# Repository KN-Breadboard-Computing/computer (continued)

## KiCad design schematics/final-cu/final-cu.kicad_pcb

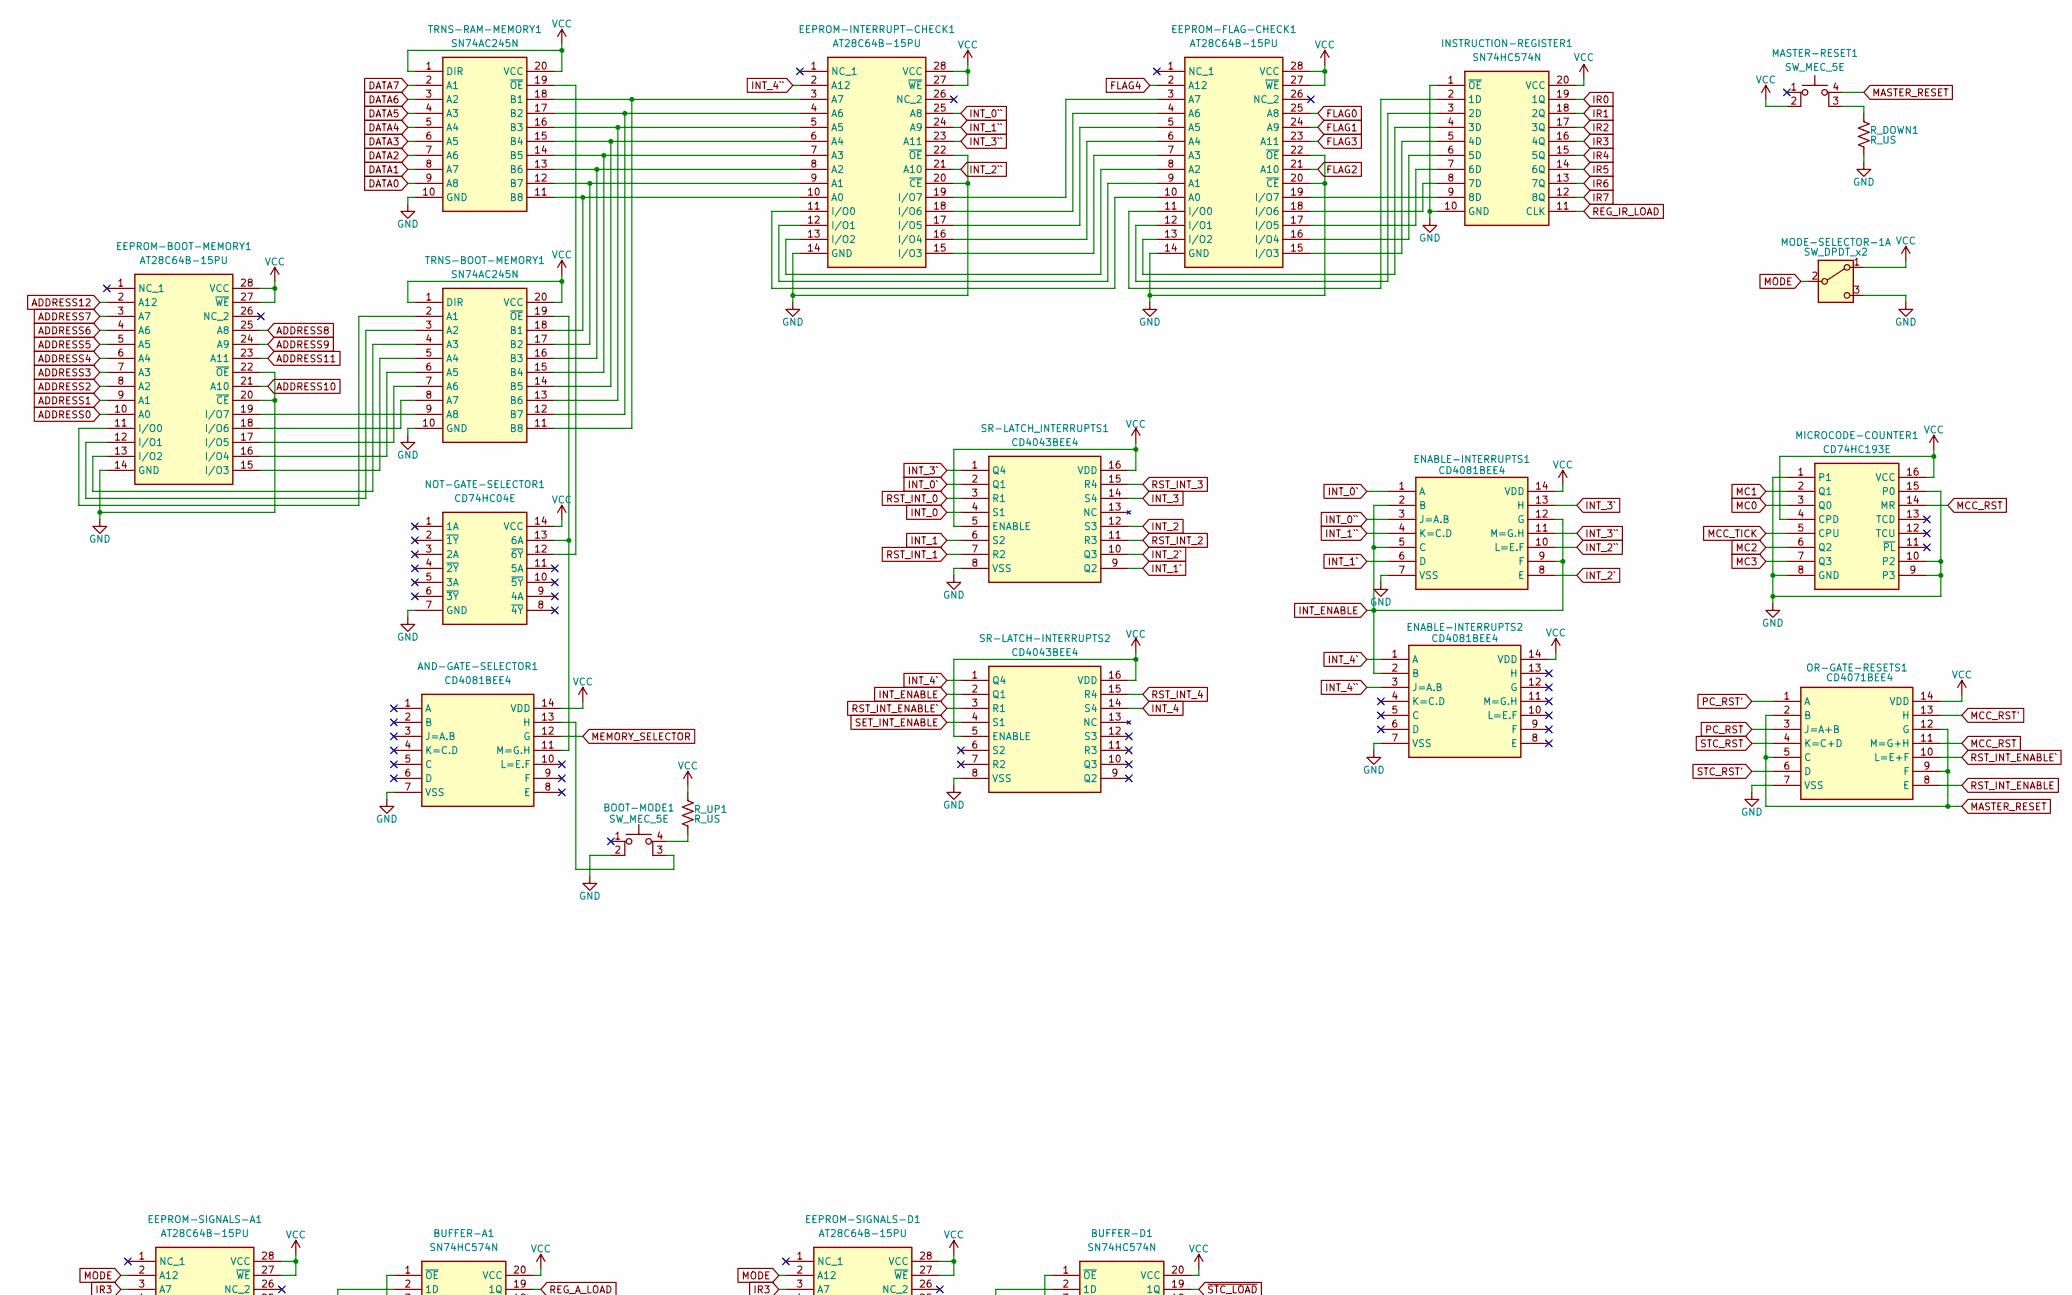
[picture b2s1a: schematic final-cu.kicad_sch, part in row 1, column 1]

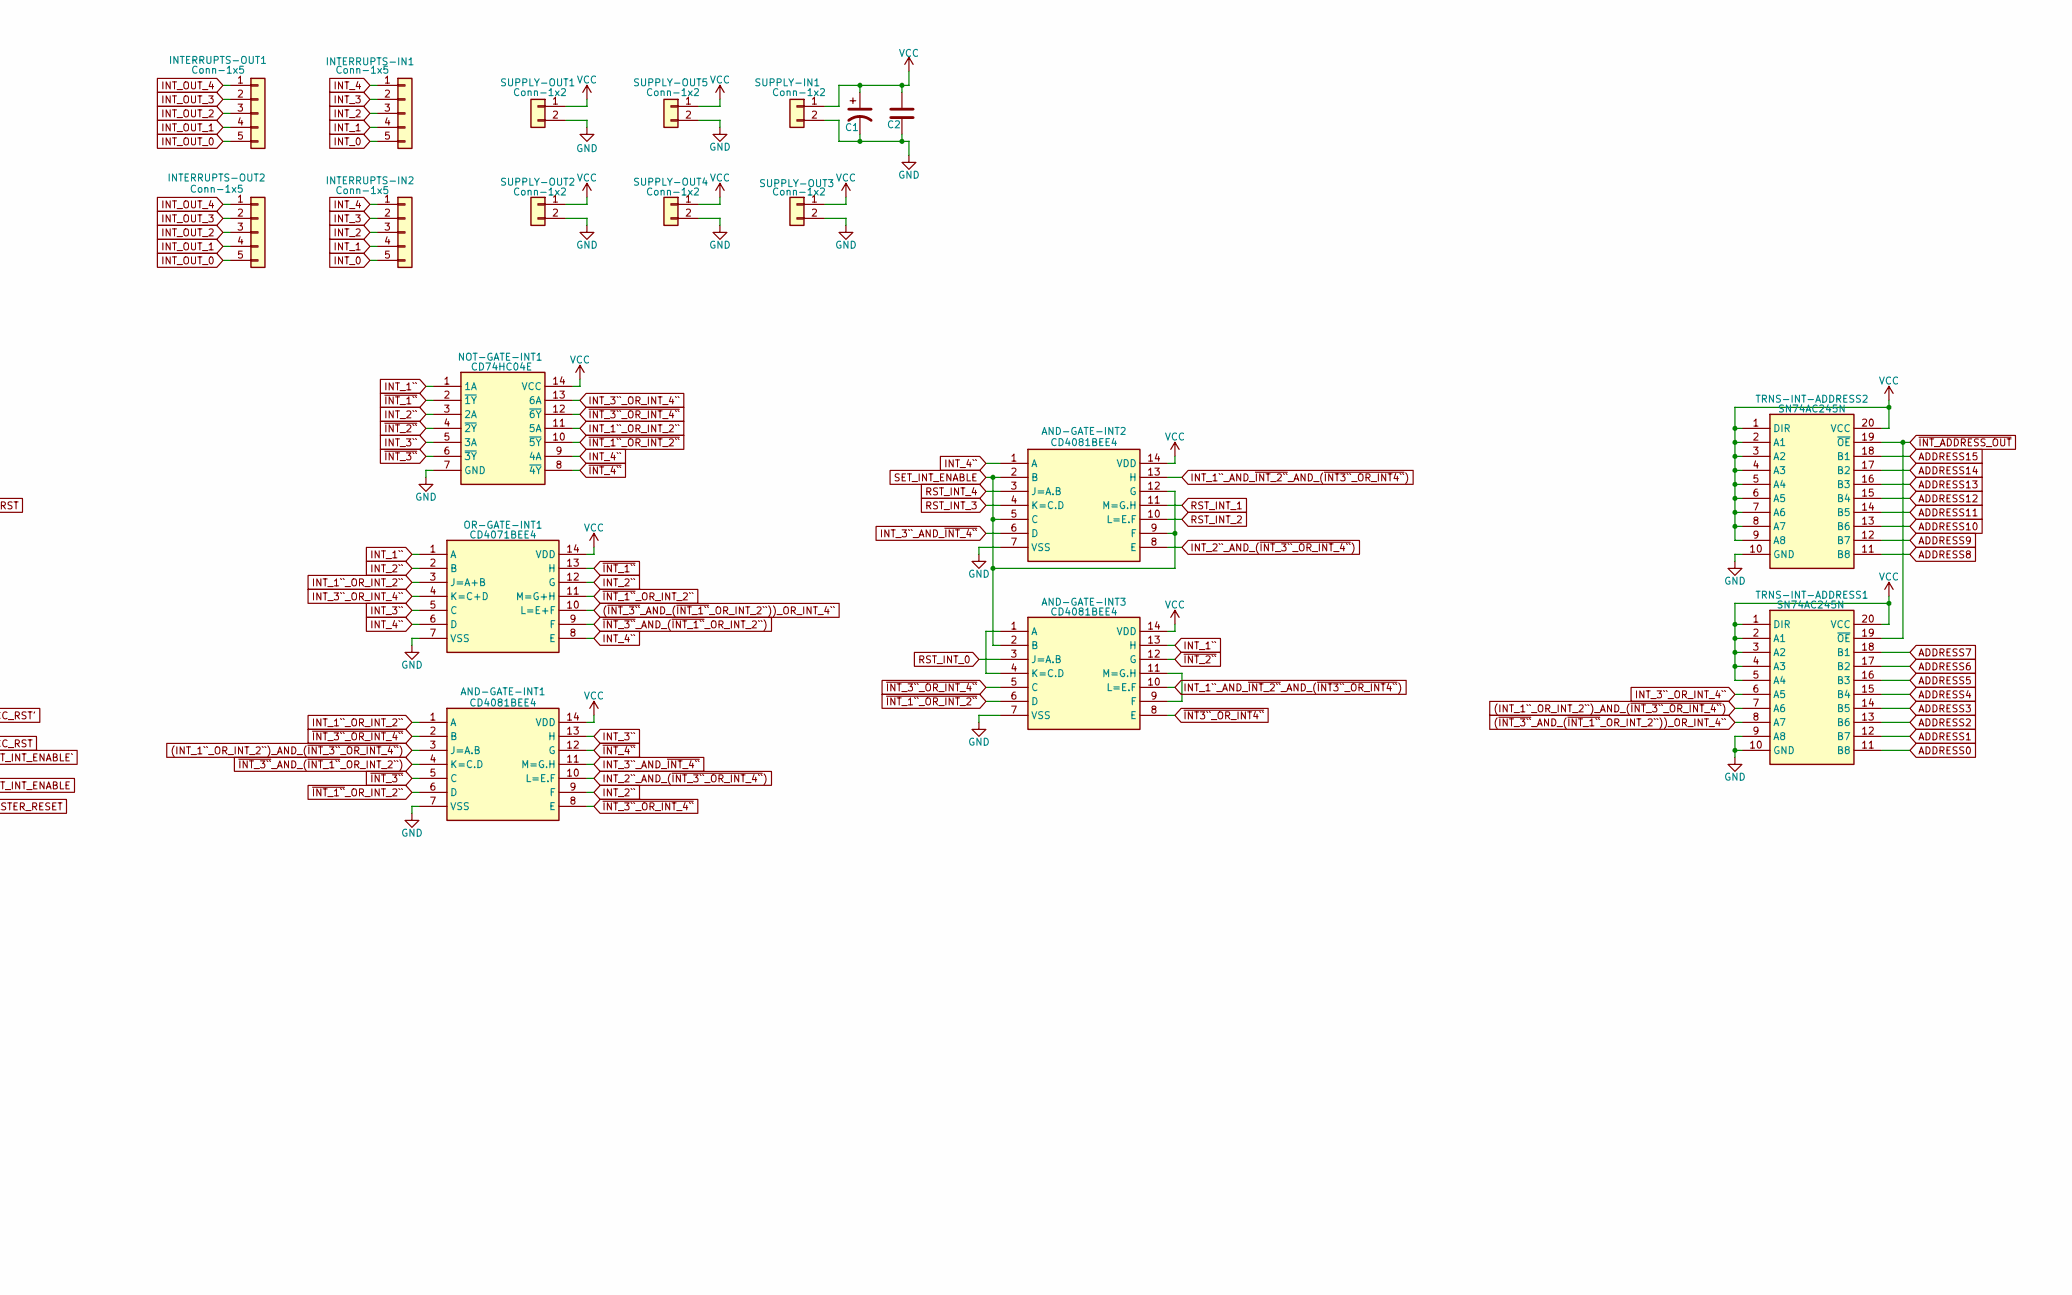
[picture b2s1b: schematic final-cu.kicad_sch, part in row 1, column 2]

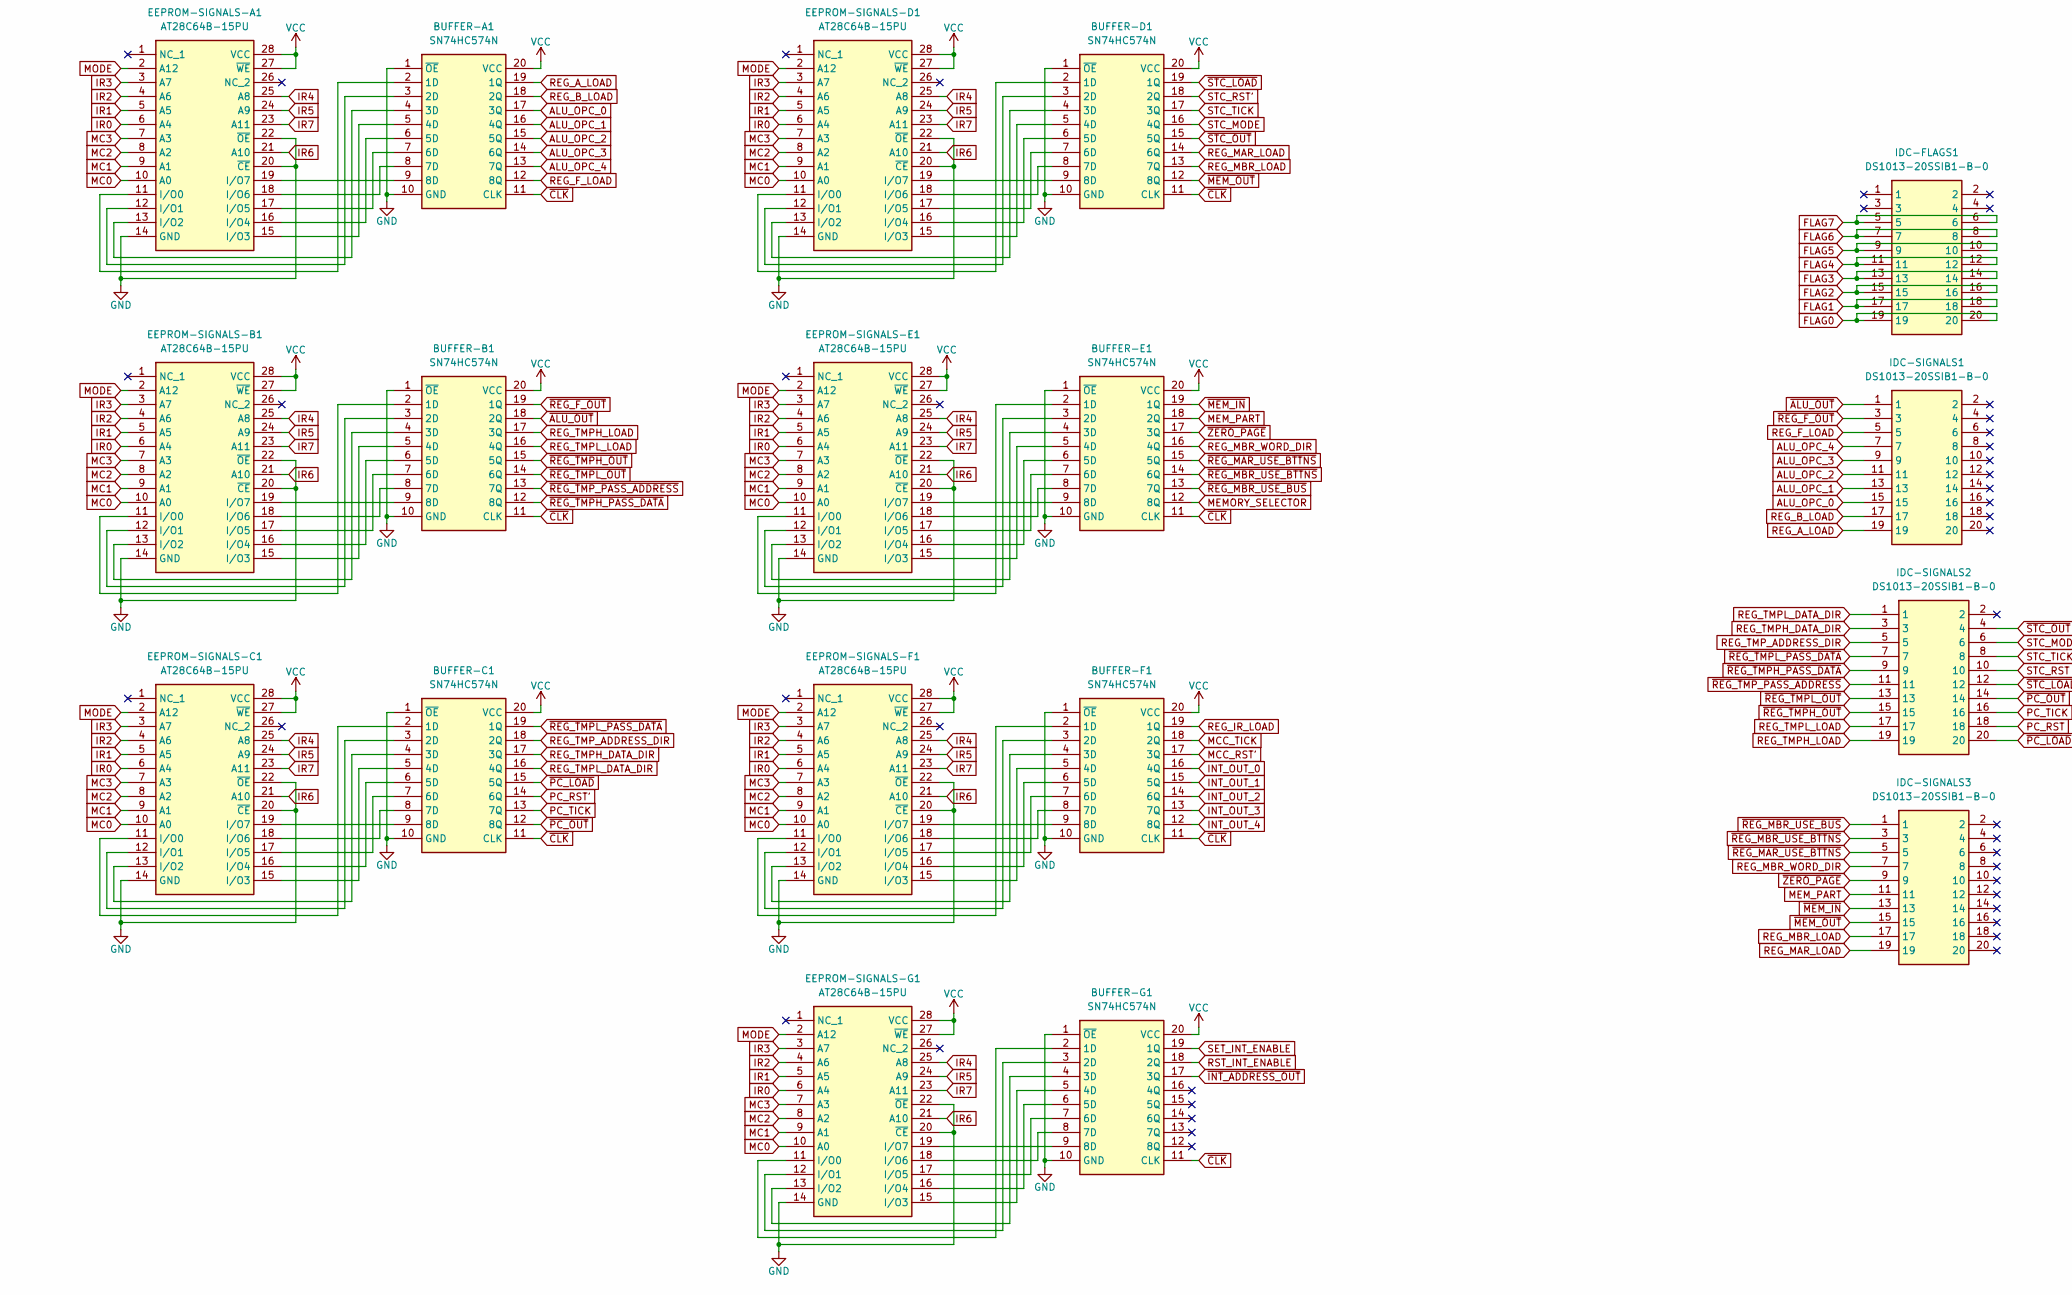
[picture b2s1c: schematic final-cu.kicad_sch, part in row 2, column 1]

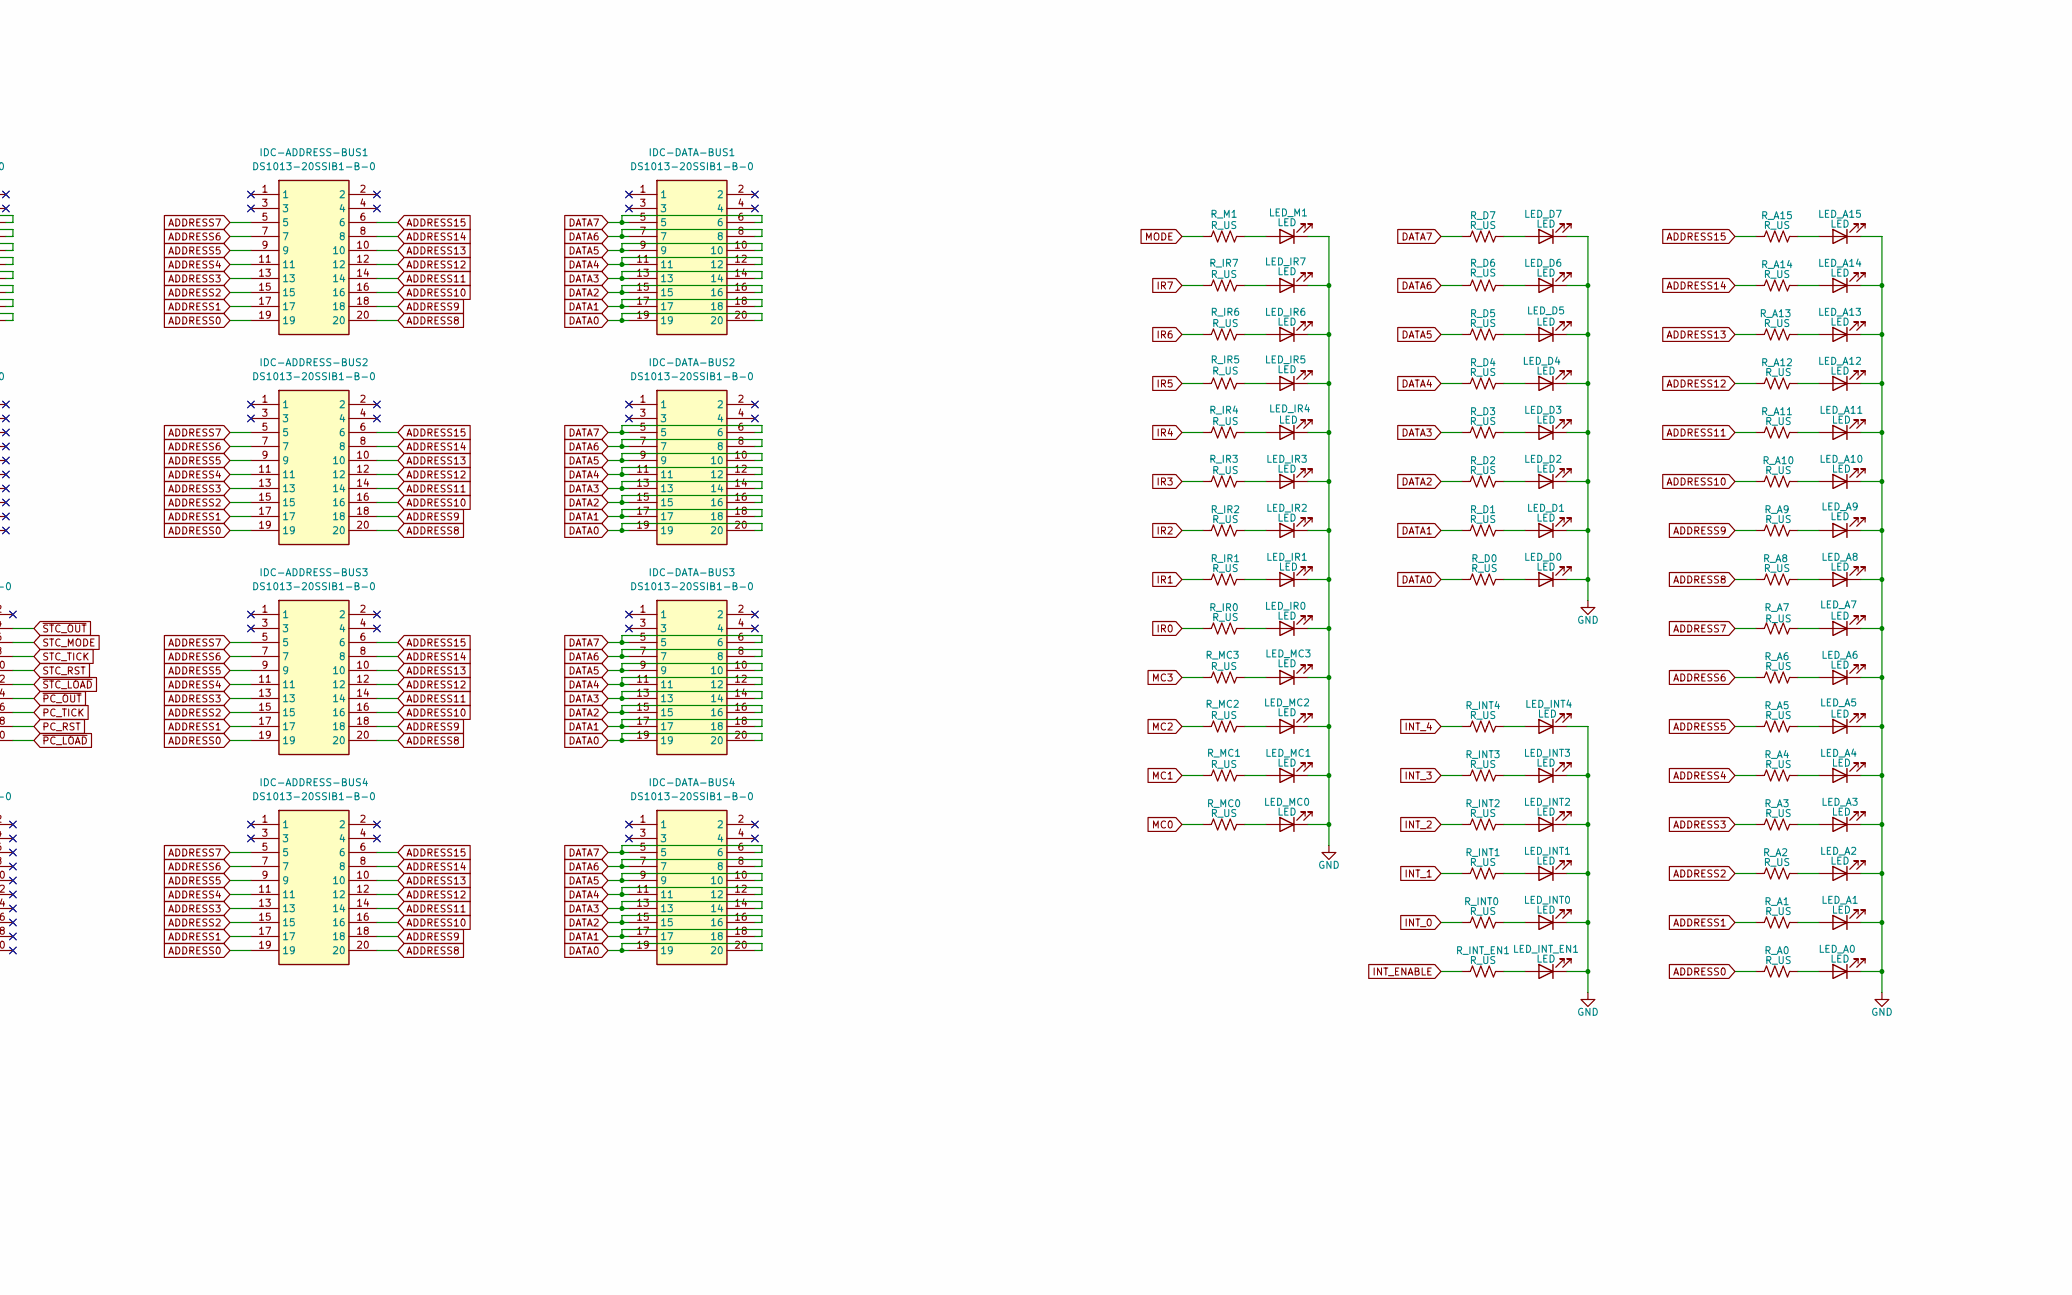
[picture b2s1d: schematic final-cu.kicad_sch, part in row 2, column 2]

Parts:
AND-GATE-INT1, AND-GATE-INT2, AND-GATE-INT3: CD4081BEE4; DIP-14_W7.62mm; Mouser Part Number 595-CD4081BEE4
AND-GATE-SELECTOR1: CD4081BEE4; DIP-14_W7.62mm; Mouser Part Number 595-CD4081BEE4
BOOT-MODE1: SW_MEC_5E; SW_Push_2P1T_Toggle_CK_PVA1xxH1xxxxxxV2
BUFFER-A1: SN74HC574N; DIP-20_W7.62mm; Mouser Part Number 595-SN74HC574N
BUFFER-B1: SN74HC574N; DIP-20_W7.62mm; Mouser Part Number 595-SN74HC574N
BUFFER-C1: SN74HC574N; DIP-20_W7.62mm; Mouser Part Number 595-SN74HC574N
BUFFER-D1: SN74HC574N; DIP-20_W7.62mm; Mouser Part Number 595-SN74HC574N
BUFFER-E1: SN74HC574N; DIP-20_W7.62mm; Mouser Part Number 595-SN74HC574N
BUFFER-F1: SN74HC574N; DIP-20_W7.62mm; Mouser Part Number 595-SN74HC574N
BUFFER-G1: SN74HC574N; DIP-20_W7.62mm; Mouser Part Number 595-SN74HC574N
C1: C_Polarized_US; CP_Radial_D5.0mm_P2.50mm
C2: C; C_Disc_D3.0mm_W1.6mm_P2.50mm
EEPROM-BOOT-MEMORY1: AT28C64B-15PU; DIP-28_W15.24mm; Mouser Part Number 556-AT28C64B15PU
EEPROM-FLAG-CHECK1: AT28C64B-15PU; DIP-28_W15.24mm; Mouser Part Number 556-AT28C64B15PU
EEPROM-INTERRUPT-CHECK1: AT28C64B-15PU; DIP-28_W15.24mm; Mouser Part Number 556-AT28C64B15PU
EEPROM-SIGNALS-A1: AT28C64B-15PU; DIP-28_W15.24mm; Mouser Part Number 556-AT28C64B15PU
EEPROM-SIGNALS-B1: AT28C64B-15PU; DIP-28_W15.24mm; Mouser Part Number 556-AT28C64B15PU
EEPROM-SIGNALS-C1: AT28C64B-15PU; DIP-28_W15.24mm; Mouser Part Number 556-AT28C64B15PU
EEPROM-SIGNALS-D1: AT28C64B-15PU; DIP-28_W15.24mm; Mouser Part Number 556-AT28C64B15PU
EEPROM-SIGNALS-E1: AT28C64B-15PU; DIP-28_W15.24mm; Mouser Part Number 556-AT28C64B15PU
EEPROM-SIGNALS-F1: AT28C64B-15PU; DIP-28_W15.24mm; Mouser Part Number 556-AT28C64B15PU
EEPROM-SIGNALS-G1: AT28C64B-15PU; DIP-28_W15.24mm; Mouser Part Number 556-AT28C64B15PU
ENABLE-INTERRUPTS1, ENABLE-INTERRUPTS2: CD4081BEE4; DIP-14_W7.62mm; Mouser Part Number 595-CD4081BEE4
IDC-ADDRESS-BUS1, IDC-ADDRESS-BUS2, IDC-ADDRESS-BUS3, IDC-ADDRESS-BUS4: DS1013-20SSIB1-B-0; PinSocket_2x10_P2.54mm_Vertical; Manufacturer_Part_Number DS1013-20SSIB1-B-0
IDC-DATA-BUS1, IDC-DATA-BUS2, IDC-DATA-BUS3, IDC-DATA-BUS4: DS1013-20SSIB1-B-0; PinSocket_2x10_P2.54mm_Vertical; Manufacturer_Part_Number DS1013-20SSIB1-B-0
IDC-FLAGS1: DS1013-20SSIB1-B-0; PinSocket_2x10_P2.54mm_Vertical; Manufacturer_Part_Number DS1013-20SSIB1-B-0
IDC-SIGNALS1, IDC-SIGNALS2, IDC-SIGNALS3: DS1013-20SSIB1-B-0; PinSocket_2x10_P2.54mm_Vertical; Manufacturer_Part_Number DS1013-20SSIB1-B-0
INSTRUCTION-REGISTER1: SN74HC574N; DIP-20_W7.62mm; Mouser Part Number 595-SN74HC574N
INTERRUPTS-IN1, INTERRUPTS-IN2: Conn-1x5; PinHeader_1x05_P2.54mm_Vertical
INTERRUPTS-OUT1, INTERRUPTS-OUT2: Conn-1x5; PinHeader_1x05_P2.54mm_Vertical
LED_A0, LED_A1, LED_A2, LED_A3, LED_A4, LED_A5, LED_A6, LED_A7, LED_A8, LED_A9, LED_A10, LED_A11, LED_A12, LED_A13, LED_A14, LED_A15: LED; LED_D5.0mm_FlatTop
LED_D0, LED_D1, LED_D2, LED_D3, LED_D4, LED_D5, LED_D6, LED_D7: LED; LED_D5.0mm_FlatTop
LED_INT0, LED_INT1, LED_INT2, LED_INT3, LED_INT4: LED; LED_D5.0mm_FlatTop
LED_INT_EN1: LED; LED_D5.0mm_FlatTop
LED_IR0, LED_IR1, LED_IR2, LED_IR3, LED_IR4, LED_IR5, LED_IR6, LED_IR7: LED; LED_D5.0mm_FlatTop
LED_M1: LED; LED_D5.0mm_FlatTop
LED_MC0, LED_MC1, LED_MC2, LED_MC3: LED; LED_D5.0mm_FlatTop
MASTER-RESET1: SW_MEC_5E; SW_Push_2P1T_Toggle_CK_PVA1xxH1xxxxxxV2
MICROCODE-COUNTER1: CD74HC193E; DIP-16_W7.62mm; Mouser Part Number 595-CD74HC193E
MODE-SELECTOR-1: SW_DPDT_x2; SW_Slide-03_Wuerth-WS-SLTV_10x2.5x6.4_P2.54mm
NOT-GATE-INT1: CD74HC04E; DIP-14_W7.62mm; Mouser Part Number 595-CD74HC04E
NOT-GATE-SELECTOR1: CD74HC04E; DIP-14_W7.62mm; Mouser Part Number 595-CD74HC04E
OR-GATE-INT1: CD4071BEE4; DIP-14_W7.62mm; Mouser Part Number 595-CD4071BEE4
OR-GATE-RESETS1: CD4071BEE4; DIP-14_W7.62mm; Mouser Part Number 595-CD4071BEE4
R_A0, R_A1, R_A2, R_A3, R_A4, R_A5, R_A6, R_A7, R_A8, R_A9, R_A10, R_A11, R_A12, R_A13, R_A14, R_A15: R_US; R_Axial_DIN0204_L3.6mm_D1.6mm_P7.62mm_Horizontal
R_D0, R_D1, R_D2, R_D3, R_D4, R_D5, R_D6, R_D7: R_US; R_Axial_DIN0204_L3.6mm_D1.6mm_P7.62mm_Horizontal
R_DOWN1: R_US; R_Axial_DIN0204_L3.6mm_D1.6mm_P7.62mm_Horizontal
R_INT0, R_INT1, R_INT2, R_INT3, R_INT4: R_US; R_Axial_DIN0204_L3.6mm_D1.6mm_P7.62mm_Horizontal
R_INT_EN1: R_US; R_Axial_DIN0204_L3.6mm_D1.6mm_P7.62mm_Horizontal
R_IR0, R_IR1, R_IR2, R_IR3, R_IR4, R_IR5, R_IR6, R_IR7: R_US; R_Axial_DIN0204_L3.6mm_D1.6mm_P7.62mm_Horizontal
R_M1: R_US; R_Axial_DIN0204_L3.6mm_D1.6mm_P7.62mm_Horizontal
R_MC0, R_MC1, R_MC2, R_MC3: R_US; R_Axial_DIN0204_L3.6mm_D1.6mm_P7.62mm_Horizontal
R_UP1: R_US; R_Axial_DIN0204_L3.6mm_D1.6mm_P7.62mm_Horizontal
SR-LATCH-INTERRUPTS2: CD4043BEE4; DIP-16_W7.62mm; Mouser Part Number 595-CD4043BEE4
SR-LATCH_INTERRUPTS1: CD4043BEE4; DIP-16_W7.62mm; Mouser Part Number 595-CD4043BEE4
SUPPLY-IN1: Conn-1x2; PinHeader_1x02_P2.54mm_Vertical
SUPPLY-OUT1, SUPPLY-OUT2, SUPPLY-OUT3, SUPPLY-OUT4, SUPPLY-OUT5: Conn-1x2; PinHeader_1x02_P2.54mm_Vertical
TRNS-BOOT-MEMORY1: SN74AC245N; DIP-20_W7.62mm; Mouser Part Number 595-SN74AC245N
TRNS-INT-ADDRESS1, TRNS-INT-ADDRESS2: SN74AC245N; DIP-20_W7.62mm; Mouser Part Number 595-SN74AC245N
TRNS-RAM-MEMORY1: SN74AC245N; DIP-20_W7.62mm; Mouser Part Number 595-SN74AC245N

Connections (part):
(INT_1``_OR_INT_2``)_AND_(~INT_3``_OR_INT_4``): AND-GATE-INT1.3 (J=A.B), TRNS-INT-ADDRESS1.7 (A6)
(~INT_3``_AND_(~INT_1``_OR_INT_2``))_OR_INT_4``: OR-GATE-INT1.10 (L=E+F), TRNS-INT-ADDRESS1.8 (A7)
ADDRESS0: EEPROM-BOOT-MEMORY1.10 (A0), IDC-ADDRESS-BUS1.19, IDC-ADDRESS-BUS2.19, IDC-ADDRESS-BUS3.19, IDC-ADDRESS-BUS4.19, R_A0.1, TRNS-INT-ADDRESS1.11 (B8)
ADDRESS1: EEPROM-BOOT-MEMORY1.9 (A1), IDC-ADDRESS-BUS1.17, IDC-ADDRESS-BUS2.17, IDC-ADDRESS-BUS3.17, IDC-ADDRESS-BUS4.17, R_A1.1, TRNS-INT-ADDRESS1.12 (B7)
ADDRESS2: EEPROM-BOOT-MEMORY1.8 (A2), IDC-ADDRESS-BUS1.15, IDC-ADDRESS-BUS2.15, IDC-ADDRESS-BUS3.15, IDC-ADDRESS-BUS4.15, R_A2.1, TRNS-INT-ADDRESS1.13 (B6)
ADDRESS3: EEPROM-BOOT-MEMORY1.7 (A3), IDC-ADDRESS-BUS1.13, IDC-ADDRESS-BUS2.13, IDC-ADDRESS-BUS3.13, IDC-ADDRESS-BUS4.13, R_A3.1, TRNS-INT-ADDRESS1.14 (B5)
ADDRESS4: EEPROM-BOOT-MEMORY1.6 (A4), IDC-ADDRESS-BUS1.11, IDC-ADDRESS-BUS2.11, IDC-ADDRESS-BUS3.11, IDC-ADDRESS-BUS4.11, R_A4.1, TRNS-INT-ADDRESS1.15 (B4)
ADDRESS5: EEPROM-BOOT-MEMORY1.5 (A5), IDC-ADDRESS-BUS1.9, IDC-ADDRESS-BUS2.9, IDC-ADDRESS-BUS3.9, IDC-ADDRESS-BUS4.9, R_A5.1, TRNS-INT-ADDRESS1.16 (B3)
ADDRESS6: EEPROM-BOOT-MEMORY1.4 (A6), IDC-ADDRESS-BUS1.7, IDC-ADDRESS-BUS2.7, IDC-ADDRESS-BUS3.7, IDC-ADDRESS-BUS4.7, R_A6.1, TRNS-INT-ADDRESS1.17 (B2)
ADDRESS7: EEPROM-BOOT-MEMORY1.3 (A7), IDC-ADDRESS-BUS1.5, IDC-ADDRESS-BUS2.5, IDC-ADDRESS-BUS3.5, IDC-ADDRESS-BUS4.5, R_A7.1, TRNS-INT-ADDRESS1.18 (B1)
ADDRESS8: EEPROM-BOOT-MEMORY1.25 (A8), IDC-ADDRESS-BUS1.20, IDC-ADDRESS-BUS2.20, IDC-ADDRESS-BUS3.20, IDC-ADDRESS-BUS4.20, R_A8.1, TRNS-INT-ADDRESS2.11 (B8)
ADDRESS9: EEPROM-BOOT-MEMORY1.24 (A9), IDC-ADDRESS-BUS1.18, IDC-ADDRESS-BUS2.18, IDC-ADDRESS-BUS3.18, IDC-ADDRESS-BUS4.18, R_A9.1, TRNS-INT-ADDRESS2.12 (B7)
ADDRESS10: EEPROM-BOOT-MEMORY1.21 (A10), IDC-ADDRESS-BUS1.16, IDC-ADDRESS-BUS2.16, IDC-ADDRESS-BUS3.16, IDC-ADDRESS-BUS4.16, R_A10.1, TRNS-INT-ADDRESS2.13 (B6)
ADDRESS11: EEPROM-BOOT-MEMORY1.23 (A11), IDC-ADDRESS-BUS1.14, IDC-ADDRESS-BUS2.14, IDC-ADDRESS-BUS3.14, IDC-ADDRESS-BUS4.14, R_A11.1, TRNS-INT-ADDRESS2.14 (B5)
ADDRESS12: EEPROM-BOOT-MEMORY1.2 (A12), IDC-ADDRESS-BUS1.12, IDC-ADDRESS-BUS2.12, IDC-ADDRESS-BUS3.12, IDC-ADDRESS-BUS4.12, R_A12.1, TRNS-INT-ADDRESS2.15 (B4)
ADDRESS13: IDC-ADDRESS-BUS1.10, IDC-ADDRESS-BUS2.10, IDC-ADDRESS-BUS3.10, IDC-ADDRESS-BUS4.10, R_A13.1, TRNS-INT-ADDRESS2.16 (B3)
ADDRESS14: IDC-ADDRESS-BUS1.8, IDC-ADDRESS-BUS2.8, IDC-ADDRESS-BUS3.8, IDC-ADDRESS-BUS4.8, R_A14.1, TRNS-INT-ADDRESS2.17 (B2)
ADDRESS15: IDC-ADDRESS-BUS1.6, IDC-ADDRESS-BUS2.6, IDC-ADDRESS-BUS3.6, IDC-ADDRESS-BUS4.6, R_A15.2, TRNS-INT-ADDRESS2.18 (B1)
ALU_OPC_0: BUFFER-A1.17 (3Q), IDC-SIGNALS1.15
ALU_OPC_1: BUFFER-A1.16 (4Q), IDC-SIGNALS1.13
ALU_OPC_2: BUFFER-A1.15 (5Q), IDC-SIGNALS1.11
ALU_OPC_3: BUFFER-A1.14 (6Q), IDC-SIGNALS1.9
ALU_OPC_4: BUFFER-A1.13 (7Q), IDC-SIGNALS1.7
DATA0: IDC-DATA-BUS1.19, IDC-DATA-BUS1.20, IDC-DATA-BUS2.19, IDC-DATA-BUS2.20, IDC-DATA-BUS3.19, IDC-DATA-BUS3.20, IDC-DATA-BUS4.19, IDC-DATA-BUS4.20, R_D0.1, TRNS-RAM-MEMORY1.9 (A8)
DATA1: IDC-DATA-BUS1.17, IDC-DATA-BUS1.18, IDC-DATA-BUS2.17, IDC-DATA-BUS2.18, IDC-DATA-BUS3.17, IDC-DATA-BUS3.18, IDC-DATA-BUS4.17, IDC-DATA-BUS4.18, R_D1.1, TRNS-RAM-MEMORY1.8 (A7)
DATA2: IDC-DATA-BUS1.15, IDC-DATA-BUS1.16, IDC-DATA-BUS2.15, IDC-DATA-BUS2.16, IDC-DATA-BUS3.15, IDC-DATA-BUS3.16, IDC-DATA-BUS4.15, IDC-DATA-BUS4.16, R_D2.1, TRNS-RAM-MEMORY1.7 (A6)
DATA3: IDC-DATA-BUS1.13, IDC-DATA-BUS1.14, IDC-DATA-BUS2.13, IDC-DATA-BUS2.14, IDC-DATA-BUS3.13, IDC-DATA-BUS3.14, IDC-DATA-BUS4.13, IDC-DATA-BUS4.14, R_D3.1, TRNS-RAM-MEMORY1.6 (A5)
DATA4: IDC-DATA-BUS1.11, IDC-DATA-BUS1.12, IDC-DATA-BUS2.11, IDC-DATA-BUS2.12, IDC-DATA-BUS3.11, IDC-DATA-BUS3.12, IDC-DATA-BUS4.11, IDC-DATA-BUS4.12, R_D4.1, TRNS-RAM-MEMORY1.5 (A4)
DATA5: IDC-DATA-BUS1.9, IDC-DATA-BUS1.10, IDC-DATA-BUS2.9, IDC-DATA-BUS2.10, IDC-DATA-BUS3.9, IDC-DATA-BUS3.10, IDC-DATA-BUS4.9, IDC-DATA-BUS4.10, R_D5.1, TRNS-RAM-MEMORY1.4 (A3)
DATA6: IDC-DATA-BUS1.7, IDC-DATA-BUS1.8, IDC-DATA-BUS2.7, IDC-DATA-BUS2.8, IDC-DATA-BUS3.7, IDC-DATA-BUS3.8, IDC-DATA-BUS4.7, IDC-DATA-BUS4.8, R_D6.1, TRNS-RAM-MEMORY1.3 (A2)
DATA7: IDC-DATA-BUS1.5, IDC-DATA-BUS1.6, IDC-DATA-BUS2.5, IDC-DATA-BUS2.6, IDC-DATA-BUS3.5, IDC-DATA-BUS3.6, IDC-DATA-BUS4.5, IDC-DATA-BUS4.6, R_D7.1, TRNS-RAM-MEMORY1.2 (A1)
FLAG0: EEPROM-FLAG-CHECK1.25 (A8), IDC-FLAGS1.19, IDC-FLAGS1.20
FLAG1: EEPROM-FLAG-CHECK1.24 (A9), IDC-FLAGS1.17, IDC-FLAGS1.18
FLAG2: EEPROM-FLAG-CHECK1.21 (A10), IDC-FLAGS1.15, IDC-FLAGS1.16
FLAG3: EEPROM-FLAG-CHECK1.23 (A11), IDC-FLAGS1.13, IDC-FLAGS1.14
FLAG4: EEPROM-FLAG-CHECK1.2 (A12), IDC-FLAGS1.11, IDC-FLAGS1.12
FLAG5: IDC-FLAGS1.9, IDC-FLAGS1.10
FLAG6: IDC-FLAGS1.7, IDC-FLAGS1.8
FLAG7: IDC-FLAGS1.5, IDC-FLAGS1.6
GND: AND-GATE-INT1.7 (VSS), AND-GATE-INT2.7 (VSS), AND-GATE-INT3.7 (VSS), AND-GATE-SELECTOR1.7 (VSS), BOOT-MODE1.2, BUFFER-A1.1 (~OE), BUFFER-A1.10 (GND), BUFFER-B1.1 (~OE), BUFFER-B1.10 (GND), BUFFER-C1.1 (~OE), BUFFER-C1.10 (GND), BUFFER-D1.1 (~OE), BUFFER-D1.10 (GND), BUFFER-E1.1 (~OE), BUFFER-E1.10 (GND), BUFFER-F1.1 (~OE), BUFFER-F1.10 (GND), BUFFER-G1.1 (~OE), BUFFER-G1.10 (GND), C1.2, C2.2, EEPROM-BOOT-MEMORY1.14 (GND), EEPROM-BOOT-MEMORY1.20 (~CE), EEPROM-BOOT-MEMORY1.22 (~OE), EEPROM-FLAG-CHECK1.14 (GND), EEPROM-FLAG-CHECK1.20 (~CE), EEPROM-FLAG-CHECK1.22 (~OE), EEPROM-INTERRUPT-CHECK1.14 (GND), EEPROM-INTERRUPT-CHECK1.20 (~CE), EEPROM-INTERRUPT-CHECK1.22 (~OE), EEPROM-SIGNALS-A1.14 (GND), EEPROM-SIGNALS-A1.20 (~CE), EEPROM-SIGNALS-A1.22 (~OE), EEPROM-SIGNALS-B1.14 (GND), EEPROM-SIGNALS-B1.20 (~CE), EEPROM-SIGNALS-B1.22 (~OE), EEPROM-SIGNALS-C1.14 (GND), EEPROM-SIGNALS-C1.20 (~CE), EEPROM-SIGNALS-C1.22 (~OE), EEPROM-SIGNALS-D1.14 (GND), EEPROM-SIGNALS-D1.20 (~CE), EEPROM-SIGNALS-D1.22 (~OE), EEPROM-SIGNALS-E1.14 (GND), EEPROM-SIGNALS-E1.20 (~CE), EEPROM-SIGNALS-E1.22 (~OE), EEPROM-SIGNALS-F1.14 (GND), EEPROM-SIGNALS-F1.20 (~CE), EEPROM-SIGNALS-F1.22 (~OE), EEPROM-SIGNALS-G1.14 (GND), EEPROM-SIGNALS-G1.20 (~CE), EEPROM-SIGNALS-G1.22 (~OE), ENABLE-INTERRUPTS1.7 (VSS), ENABLE-INTERRUPTS2.7 (VSS), INSTRUCTION-REGISTER1.1 (~OE), INSTRUCTION-REGISTER1.10 (GND), LED_A0.1 (K), LED_A1.1 (K), LED_A2.1 (K), LED_A3.1 (K), LED_A4.1 (K), LED_A5.1 (K), LED_A6.1 (K), LED_A7.1 (K), LED_A8.1 (K), LED_A9.1 (K), LED_A10.1 (K), LED_A11.1 (K), LED_A12.1 (K), LED_A13.1 (K), LED_A14.1 (K), LED_A15.1 (K), LED_D0.1 (K), LED_D1.1 (K), LED_D2.1 (K), LED_D3.1 (K), LED_D4.1 (K), LED_D5.1 (K), LED_D6.1 (K), LED_D7.1 (K), LED_INT0.1 (K)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
INT_0: INTERRUPTS-IN1.5, INTERRUPTS-IN2.5, R_INT0.1, SR-LATCH_INTERRUPTS1.4 (S1)
INT_0`: ENABLE-INTERRUPTS1.1 (A), SR-LATCH_INTERRUPTS1.2 (Q1)
INT_0``: EEPROM-INTERRUPT-CHECK1.25 (A8), ENABLE-INTERRUPTS1.3 (J=A.B)
INT_1: INTERRUPTS-IN1.4, INTERRUPTS-IN2.4, R_INT1.1, SR-LATCH_INTERRUPTS1.6 (S2)
INT_1`: ENABLE-INTERRUPTS1.6 (D), SR-LATCH_INTERRUPTS1.9 (Q2)
INT_1``: AND-GATE-INT3.13 (H), EEPROM-INTERRUPT-CHECK1.24 (A9), ENABLE-INTERRUPTS1.4 (K=C.D), NOT-GATE-INT1.1 (1A), OR-GATE-INT1.1 (A)
INT_1``_AND_~INT_2``_AND_(~INT3``_OR_INT4``): AND-GATE-INT2.13 (H), AND-GATE-INT3.10 (L=E.F)
INT_1``_OR_INT_2``: AND-GATE-INT1.1 (A), NOT-GATE-INT1.11 (5A), OR-GATE-INT1.3 (J=A+B)
INT_2: INTERRUPTS-IN1.3, INTERRUPTS-IN2.3, R_INT2.1, SR-LATCH_INTERRUPTS1.12 (S3)
INT_2`: ENABLE-INTERRUPTS1.8 (E), SR-LATCH_INTERRUPTS1.10 (Q3)
INT_2``: AND-GATE-INT1.9 (F), EEPROM-INTERRUPT-CHECK1.21 (A10), ENABLE-INTERRUPTS1.10 (L=E.F), NOT-GATE-INT1.3 (2A), OR-GATE-INT1.2 (B), OR-GATE-INT1.12 (G)
INT_2``_AND_(~INT_3``_OR_INT_4``): AND-GATE-INT1.10 (L=E.F), AND-GATE-INT2.8 (E)
INT_3: INTERRUPTS-IN1.2, INTERRUPTS-IN2.2, R_INT3.1, SR-LATCH_INTERRUPTS1.14 (S4)
INT_3`: ENABLE-INTERRUPTS1.13 (H), SR-LATCH_INTERRUPTS1.1 (Q4)
INT_3``: AND-GATE-INT1.13 (H), EEPROM-INTERRUPT-CHECK1.23 (A11), ENABLE-INTERRUPTS1.11 (M=G.H), NOT-GATE-INT1.5 (3A), OR-GATE-INT1.5 (C)
INT_3``_AND_~INT_4``: AND-GATE-INT1.11 (M=G.H), AND-GATE-INT2.6 (D)
INT_3``_OR_INT_4``: NOT-GATE-INT1.13 (6A), OR-GATE-INT1.4 (K=C+D), TRNS-INT-ADDRESS1.6 (A5)
INT_4: INTERRUPTS-IN1.1, INTERRUPTS-IN2.1, R_INT4.1, SR-LATCH-INTERRUPTS2.14 (S4)
INT_4`: ENABLE-INTERRUPTS2.1 (A), SR-LATCH-INTERRUPTS2.1 (Q4)
INT_4``: AND-GATE-INT2.1 (A), EEPROM-INTERRUPT-CHECK1.2 (A12), ENABLE-INTERRUPTS2.3 (J=A.B), NOT-GATE-INT1.9 (4A), OR-GATE-INT1.6 (D), OR-GATE-INT1.8 (E)
INT_ENABLE: ENABLE-INTERRUPTS1.2 (B), ENABLE-INTERRUPTS1.5 (C), ENABLE-INTERRUPTS1.9 (F), ENABLE-INTERRUPTS1.12 (G), ENABLE-INTERRUPTS2.2 (B), R_INT_EN1.1, SR-LATCH-INTERRUPTS2.2 (Q1)
INT_OUT_0: BUFFER-F1.16 (4Q), INTERRUPTS-OUT1.5, INTERRUPTS-OUT2.5
INT_OUT_1: BUFFER-F1.15 (5Q), INTERRUPTS-OUT1.4, INTERRUPTS-OUT2.4
INT_OUT_2: BUFFER-F1.14 (6Q), INTERRUPTS-OUT1.3, INTERRUPTS-OUT2.3
INT_OUT_3: BUFFER-F1.13 (7Q), INTERRUPTS-OUT1.2, INTERRUPTS-OUT2.2
INT_OUT_4: BUFFER-F1.12 (8Q), INTERRUPTS-OUT1.1, INTERRUPTS-OUT2.1
IR0: EEPROM-SIGNALS-A1.6 (A4), EEPROM-SIGNALS-B1.6 (A4), EEPROM-SIGNALS-C1.6 (A4), EEPROM-SIGNALS-D1.6 (A4), EEPROM-SIGNALS-E1.6 (A4), EEPROM-SIGNALS-F1.6 (A4), EEPROM-SIGNALS-G1.6 (A4), INSTRUCTION-REGISTER1.19 (1Q), R_IR0.1
IR1: EEPROM-SIGNALS-A1.5 (A5), EEPROM-SIGNALS-B1.5 (A5), EEPROM-SIGNALS-C1.5 (A5), EEPROM-SIGNALS-D1.5 (A5), EEPROM-SIGNALS-E1.5 (A5), EEPROM-SIGNALS-F1.5 (A5), EEPROM-SIGNALS-G1.5 (A5), INSTRUCTION-REGISTER1.18 (2Q), R_IR1.1
IR2: EEPROM-SIGNALS-A1.4 (A6), EEPROM-SIGNALS-B1.4 (A6), EEPROM-SIGNALS-C1.4 (A6), EEPROM-SIGNALS-D1.4 (A6), EEPROM-SIGNALS-E1.4 (A6), EEPROM-SIGNALS-F1.4 (A6), EEPROM-SIGNALS-G1.4 (A6), INSTRUCTION-REGISTER1.17 (3Q), R_IR2.1
IR3: EEPROM-SIGNALS-A1.3 (A7), EEPROM-SIGNALS-B1.3 (A7), EEPROM-SIGNALS-C1.3 (A7), EEPROM-SIGNALS-D1.3 (A7), EEPROM-SIGNALS-E1.3 (A7), EEPROM-SIGNALS-F1.3 (A7), EEPROM-SIGNALS-G1.3 (A7), INSTRUCTION-REGISTER1.16 (4Q), R_IR3.1
IR4: EEPROM-SIGNALS-A1.25 (A8), EEPROM-SIGNALS-B1.25 (A8), EEPROM-SIGNALS-C1.25 (A8), EEPROM-SIGNALS-D1.25 (A8), EEPROM-SIGNALS-E1.25 (A8), EEPROM-SIGNALS-F1.25 (A8), EEPROM-SIGNALS-G1.25 (A8), INSTRUCTION-REGISTER1.15 (5Q), R_IR4.1
IR5: EEPROM-SIGNALS-A1.24 (A9), EEPROM-SIGNALS-B1.24 (A9), EEPROM-SIGNALS-C1.24 (A9), EEPROM-SIGNALS-D1.24 (A9), EEPROM-SIGNALS-E1.24 (A9), EEPROM-SIGNALS-F1.24 (A9), EEPROM-SIGNALS-G1.24 (A9), INSTRUCTION-REGISTER1.14 (6Q), R_IR5.1
IR6: EEPROM-SIGNALS-A1.21 (A10), EEPROM-SIGNALS-B1.21 (A10), EEPROM-SIGNALS-C1.21 (A10), EEPROM-SIGNALS-D1.21 (A10), EEPROM-SIGNALS-E1.21 (A10), EEPROM-SIGNALS-F1.21 (A10), EEPROM-SIGNALS-G1.21 (A10), INSTRUCTION-REGISTER1.13 (7Q), R_IR6.2
IR7: EEPROM-SIGNALS-A1.23 (A11), EEPROM-SIGNALS-B1.23 (A11), EEPROM-SIGNALS-C1.23 (A11), EEPROM-SIGNALS-D1.23 (A11), EEPROM-SIGNALS-E1.23 (A11), EEPROM-SIGNALS-F1.23 (A11), EEPROM-SIGNALS-G1.23 (A11), INSTRUCTION-REGISTER1.12 (8Q), R_IR7.1
MASTER_RESET: MASTER-RESET1.4 (A), OR-GATE-RESETS1.2 (B), OR-GATE-RESETS1.5 (C), OR-GATE-RESETS1.9 (F), OR-GATE-RESETS1.12 (G)
MC0: EEPROM-SIGNALS-A1.10 (A0), EEPROM-SIGNALS-B1.10 (A0), EEPROM-SIGNALS-C1.10 (A0), EEPROM-SIGNALS-D1.10 (A0), EEPROM-SIGNALS-E1.10 (A0), EEPROM-SIGNALS-F1.10 (A0), EEPROM-SIGNALS-G1.10 (A0), MICROCODE-COUNTER1.3 (Q0), R_MC0.1
MC1: EEPROM-SIGNALS-A1.9 (A1), EEPROM-SIGNALS-B1.9 (A1), EEPROM-SIGNALS-C1.9 (A1), EEPROM-SIGNALS-D1.9 (A1), EEPROM-SIGNALS-E1.9 (A1), EEPROM-SIGNALS-F1.9 (A1), EEPROM-SIGNALS-G1.9 (A1), MICROCODE-COUNTER1.2 (Q1), R_MC1.1
MC2: EEPROM-SIGNALS-A1.8 (A2), EEPROM-SIGNALS-B1.8 (A2), EEPROM-SIGNALS-C1.8 (A2), EEPROM-SIGNALS-D1.8 (A2), EEPROM-SIGNALS-E1.8 (A2), EEPROM-SIGNALS-F1.8 (A2), EEPROM-SIGNALS-G1.8 (A2), MICROCODE-COUNTER1.6 (Q2), R_MC2.1
MC3: EEPROM-SIGNALS-A1.7 (A3), EEPROM-SIGNALS-B1.7 (A3), EEPROM-SIGNALS-C1.7 (A3), EEPROM-SIGNALS-D1.7 (A3), EEPROM-SIGNALS-E1.7 (A3), EEPROM-SIGNALS-F1.7 (A3), EEPROM-SIGNALS-G1.7 (A3), MICROCODE-COUNTER1.7 (Q3), R_MC3.1
MCC_RST: MICROCODE-COUNTER1.14 (MR), OR-GATE-RESETS1.11 (M=G+H)
MCC_RST': BUFFER-F1.17 (3Q), OR-GATE-RESETS1.13 (H)
MCC_TICK: BUFFER-F1.18 (2Q), MICROCODE-COUNTER1.5 (CPU)
MEMORY_SELECTOR: AND-GATE-SELECTOR1.12 (G), BUFFER-E1.12 (8Q)
MEM_PART: BUFFER-E1.18 (2Q), IDC-SIGNALS3.11
MODE: EEPROM-SIGNALS-A1.2 (A12), EEPROM-SIGNALS-B1.2 (A12), EEPROM-SIGNALS-C1.2 (A12), EEPROM-SIGNALS-D1.2 (A12), EEPROM-SIGNALS-E1.2 (A12), EEPROM-SIGNALS-F1.2 (A12), EEPROM-SIGNALS-G1.2 (A12), MODE-SELECTOR-1.2 (B), R_M1.1
unnamed: AND-GATE-INT3.1 (A), AND-GATE-INT3.4 (K=C.D)
unnamed: AND-GATE-INT3.9 (F), AND-GATE-INT3.11 (M=G.H)
unnamed: AND-GATE-SELECTOR1.13 (H), BOOT-MODE1.3 (K)
unnamed: AND-GATE-SELECTOR1.11 (M=G.H), NOT-GATE-SELECTOR1.13 (6A), TRNS-BOOT-MEMORY1.19 (~OE)
unnamed: BOOT-MODE1.4 (A), R_UP1.2
unnamed: BUFFER-A1.2 (1D), EEPROM-SIGNALS-A1.11 (I/O0)
unnamed: BUFFER-A1.3 (2D), EEPROM-SIGNALS-A1.12 (I/O1)
unnamed: BUFFER-A1.4 (3D), EEPROM-SIGNALS-A1.13 (I/O2)
unnamed: BUFFER-A1.5 (4D), EEPROM-SIGNALS-A1.15 (I/O3)
unnamed: BUFFER-A1.6 (5D), EEPROM-SIGNALS-A1.16 (I/O4)
unnamed: BUFFER-A1.7 (6D), EEPROM-SIGNALS-A1.17 (I/O5)
unnamed: BUFFER-A1.8 (7D), EEPROM-SIGNALS-A1.18 (I/O6)
unnamed: BUFFER-A1.9 (8D), EEPROM-SIGNALS-A1.19 (I/O7)
unnamed: BUFFER-B1.2 (1D), EEPROM-SIGNALS-B1.11 (I/O0)
unnamed: BUFFER-B1.3 (2D), EEPROM-SIGNALS-B1.12 (I/O1)
unnamed: BUFFER-B1.4 (3D), EEPROM-SIGNALS-B1.13 (I/O2)
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
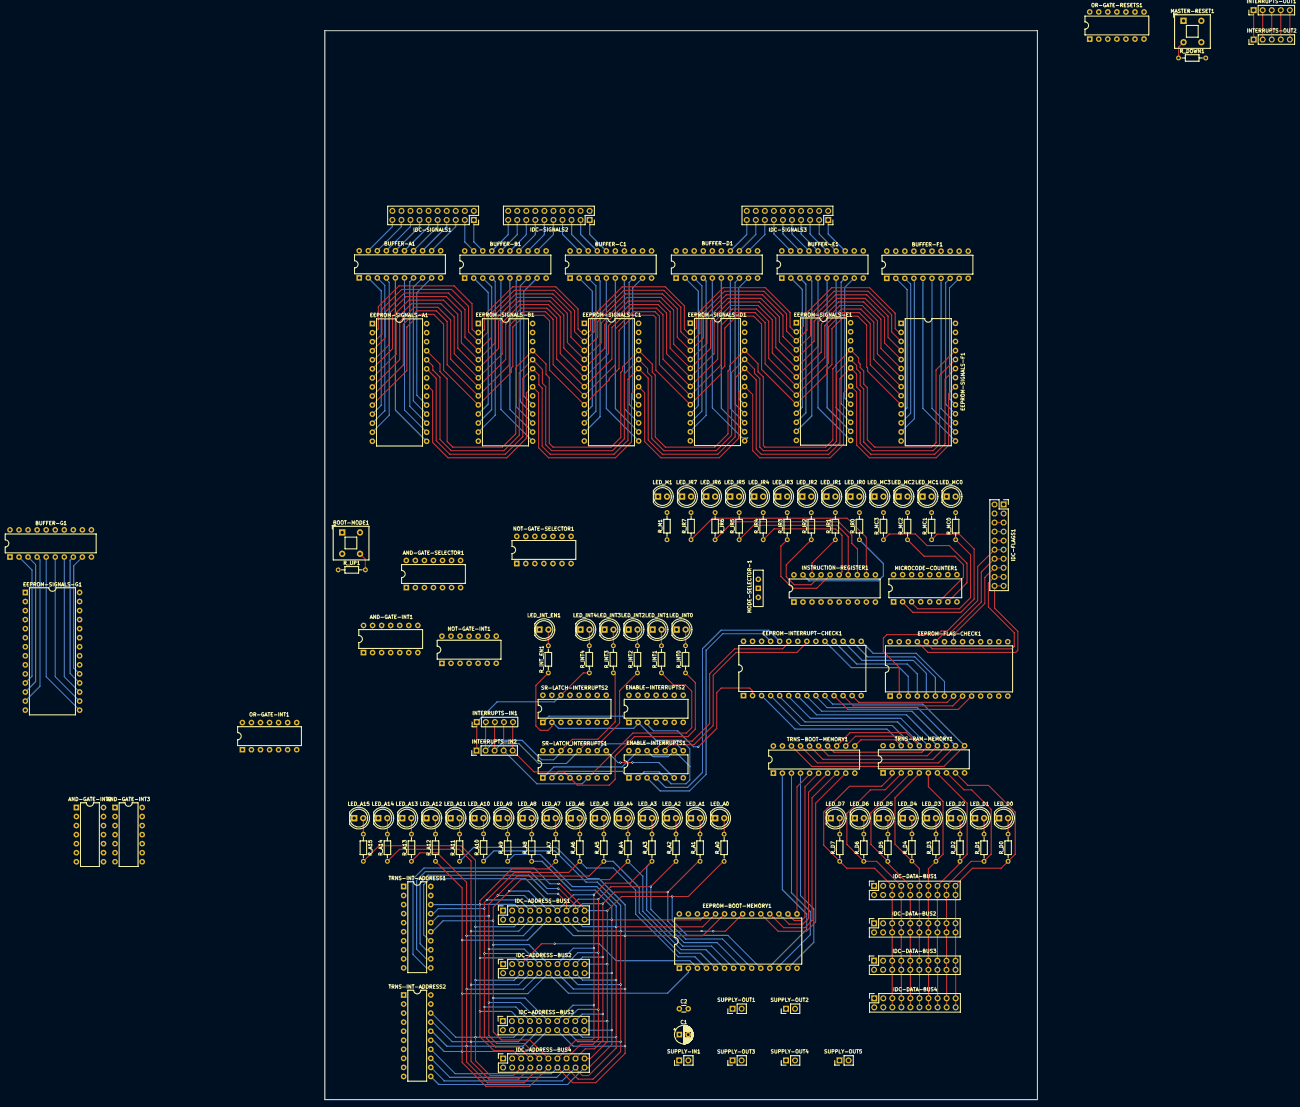
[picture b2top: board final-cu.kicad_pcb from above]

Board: 2 copper layers, 200.0 x 300.0 mm, 150 parts (0 on the bottom side), 278 nets.
